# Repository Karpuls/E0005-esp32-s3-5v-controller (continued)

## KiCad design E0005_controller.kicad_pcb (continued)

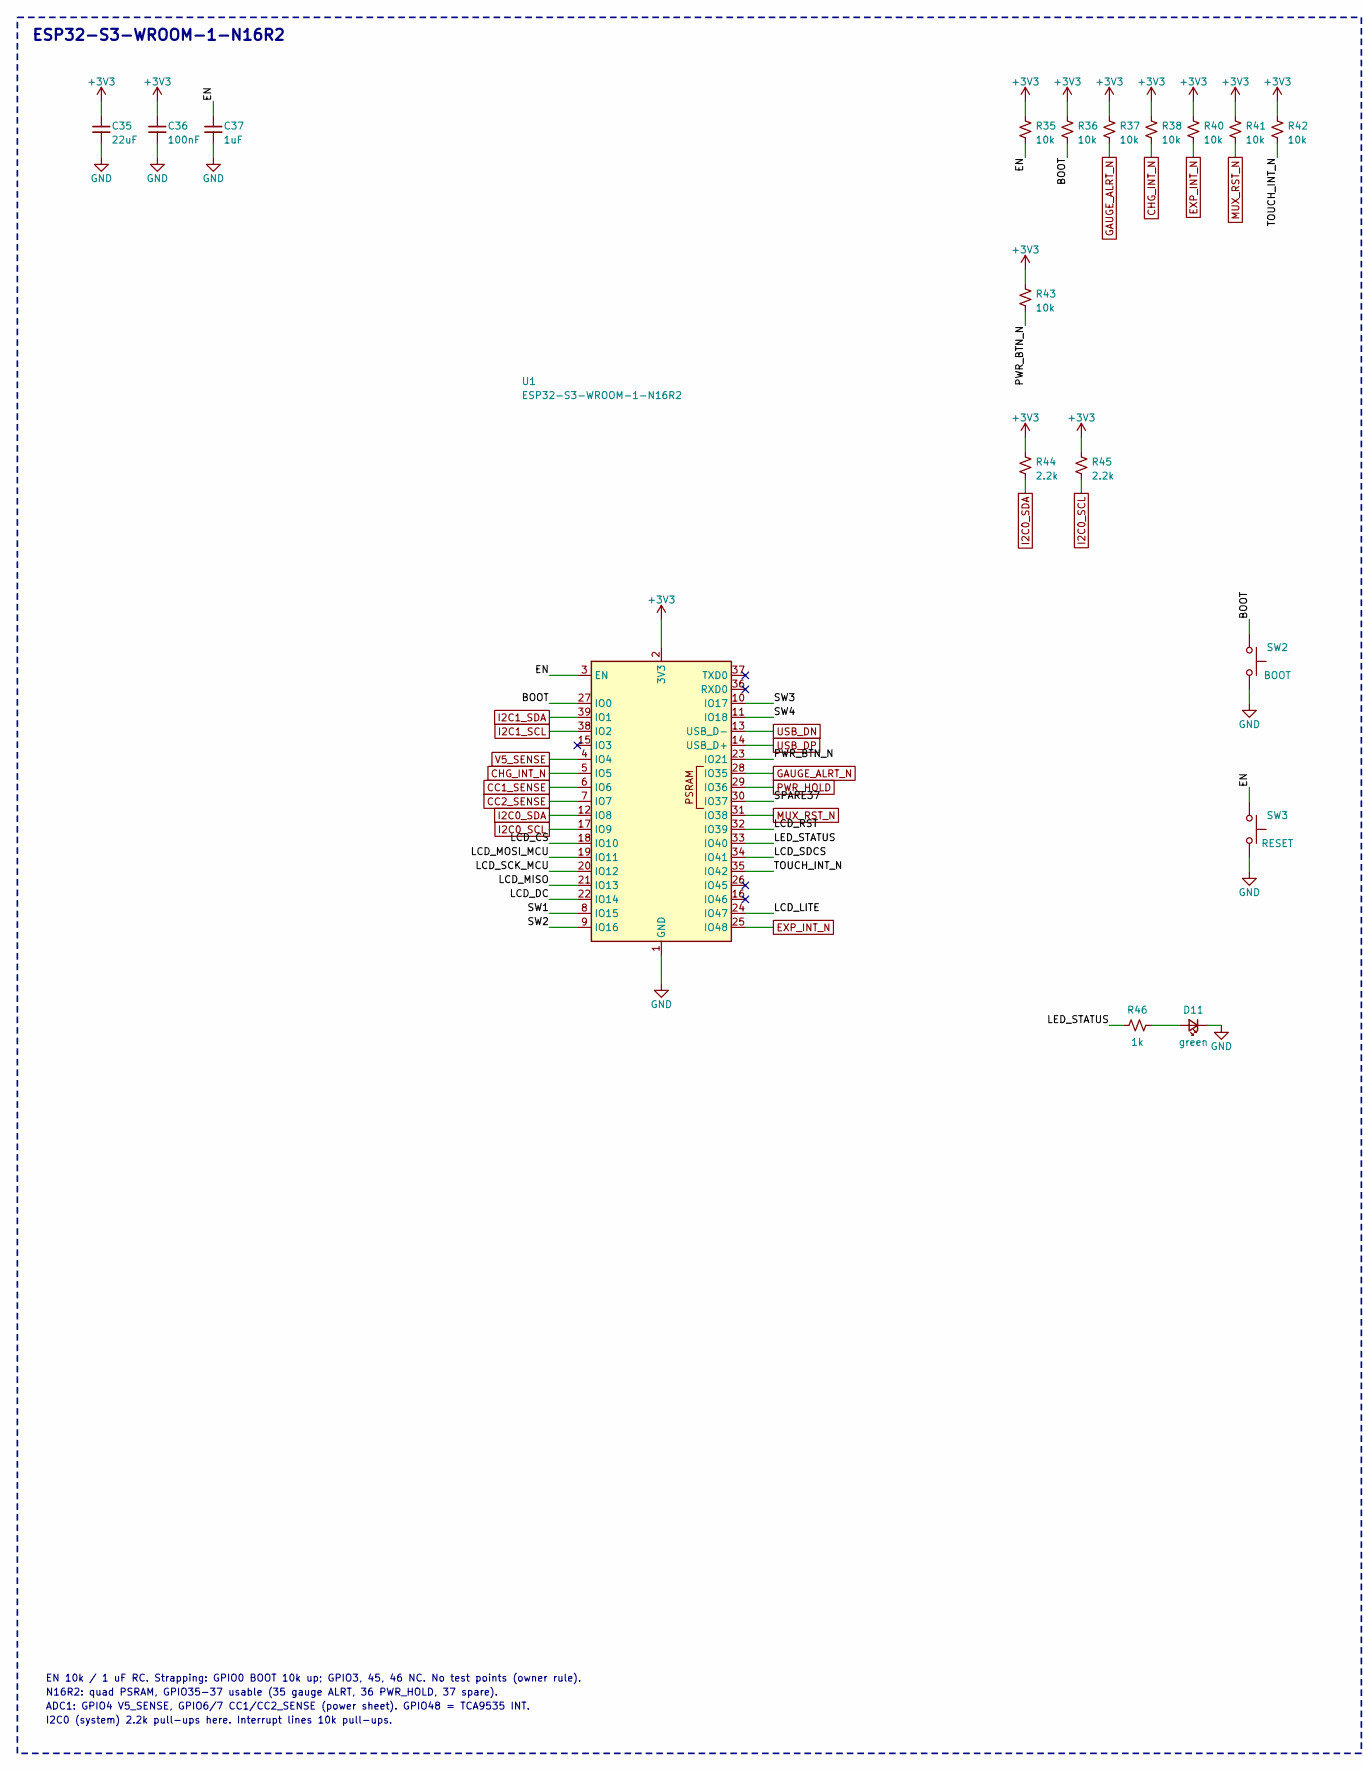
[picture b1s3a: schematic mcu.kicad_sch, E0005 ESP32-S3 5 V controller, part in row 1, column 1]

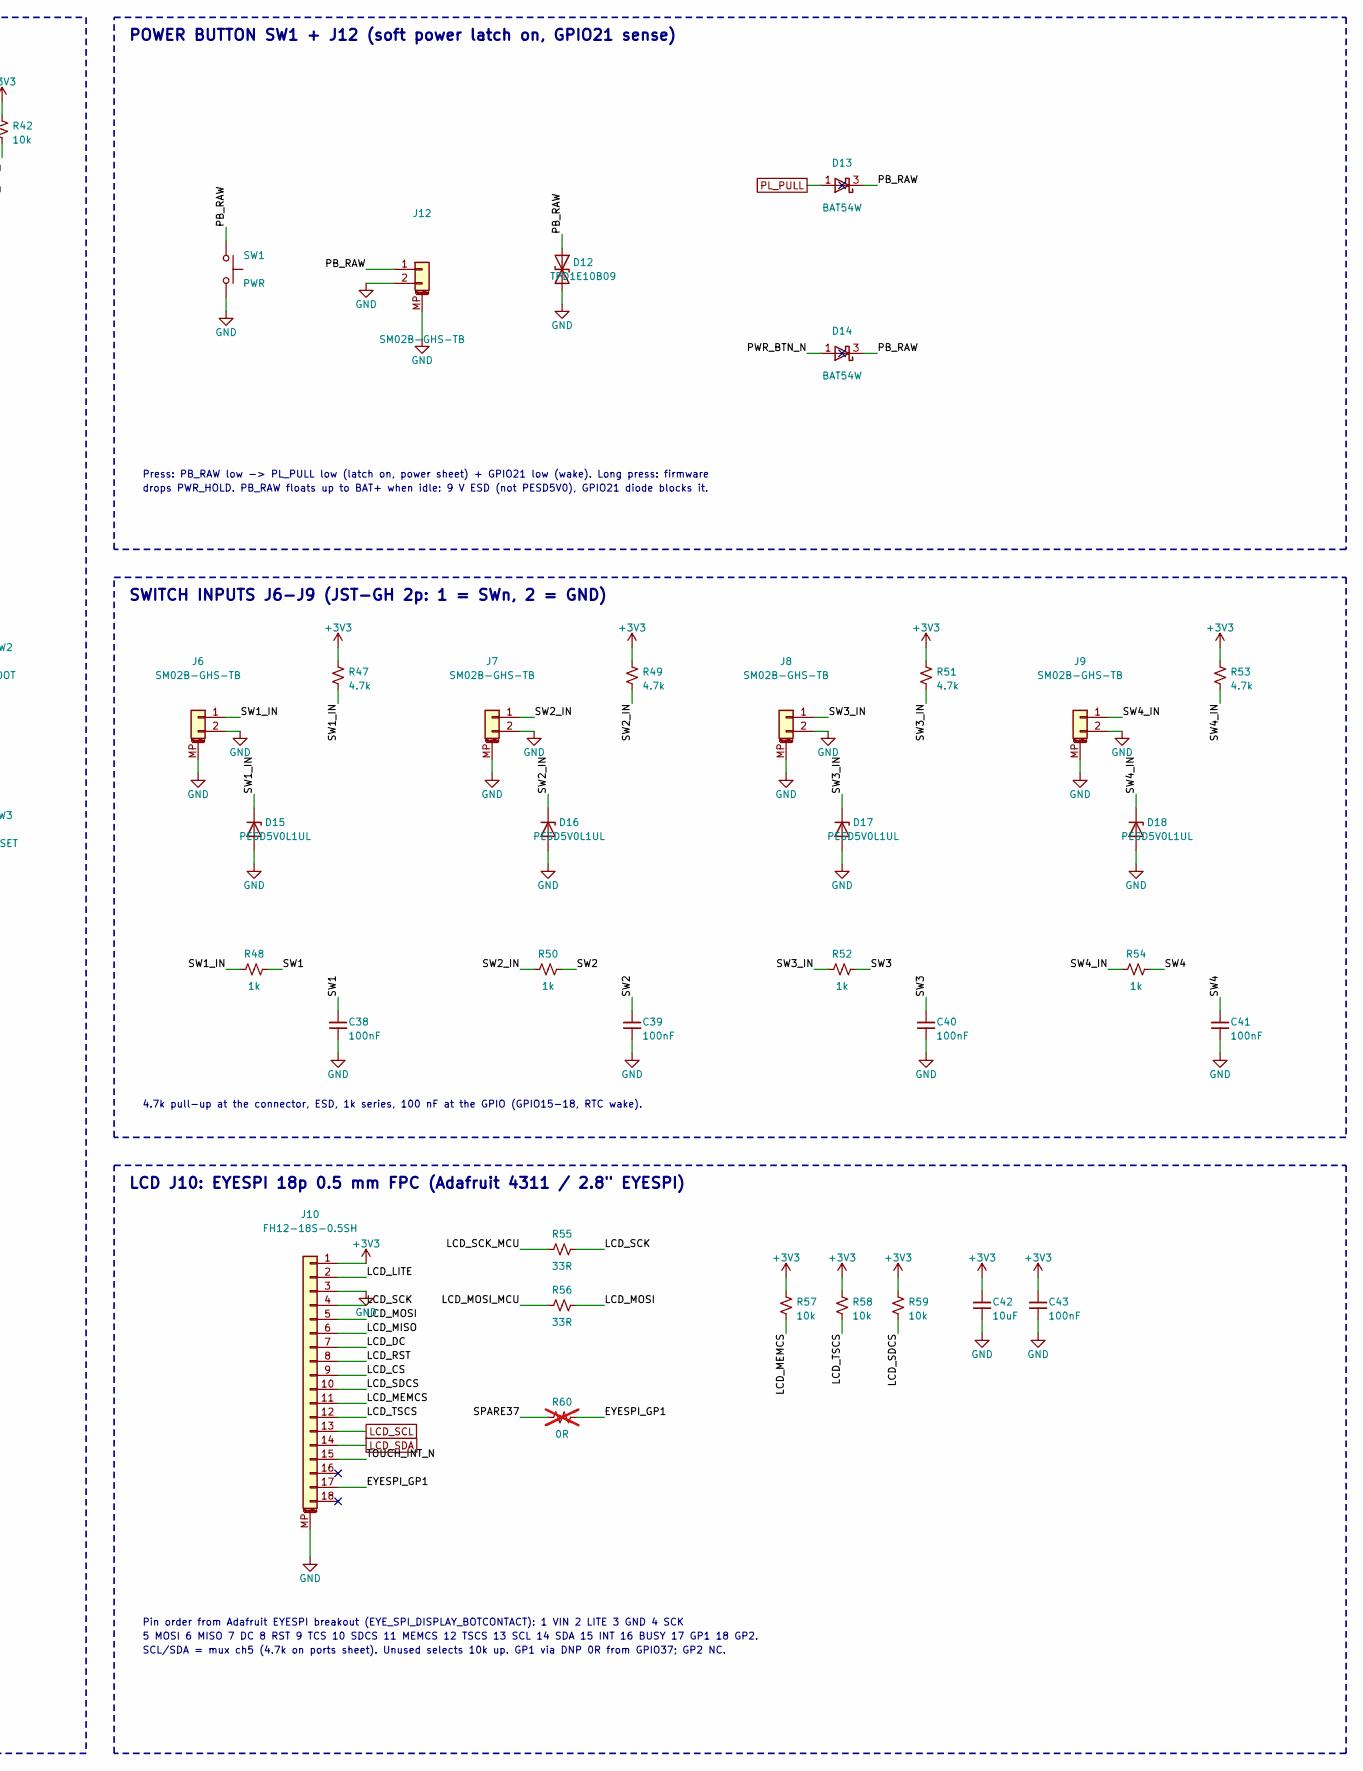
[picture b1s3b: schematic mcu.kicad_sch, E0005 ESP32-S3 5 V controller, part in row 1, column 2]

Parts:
C35: 22uF; C_0805_2012Metric; Voltage 6.3V; MPN CL21A226KQCLRNC
C36, C38, C39, C40, C41, C43: 100nF; C_0402_1005Metric; Voltage 50V; MPN GRM155R71H104KE14D
C37: 1uF; C_0402_1005Metric; MPN CL05A105KP5NNNC
C42: 10uF; C_0805_2012Metric; Voltage 25V; MPN TMK212BBJ106MG-T
D11: green; LED_0603_1608Metric; MPN LTST-C191KGKT
D12: TPD1E10B09; D_0402_1005Metric; MPN TPD1E10B09DPYR
D13, D14: BAT54W; SOT-323_SC-70; MPN BAT54W,135
D15, D16, D17, D18: PESD5V0L1UL; D_SOD-882; MPN PESD5V0L1UL,315
J6, J7, J8, J9, J12: SM02B-GHS-TB; JST_GH_SM02B-GHS-TB_1x02-1MP_P1.25mm_Horizontal; MPN SM02B-GHS-TB
J10: FH12-18S-0.5SH; Hirose_FH12-18S-0.5SH_1x18-1MP_P0.50mm_Horizontal; MPN FH12-18S-0.5SH(55)
R35, R36, R37, R38, R40, R41, R42, R43, R57, R58, R59: 10k; R_0402_1005Metric; MPN RC0402FR-0710KL
R44, R45: 2.2k; R_0402_1005Metric; MPN RC0402FR-072K2L
R46, R48, R50, R52, R54: 1k; R_0402_1005Metric; MPN RC0402FR-071KL
R47, R49, R51, R53: 4.7k; R_0402_1005Metric; MPN RK73H1ETTP4701F
R55, R56: 33R; R_0402_1005Metric; MPN RC0402FR-0733RL
R60: 0R; R_0402_1005Metric; MPN RC0402JR-070RL; not fitted
SW1: PWR; SW_SPST_PTS810; MPN PTS810SJM250SMTR LFS
SW2: BOOT; SW_SPST_PTS810; MPN PTS810SJM250SMTR LFS
SW3: RESET; SW_SPST_PTS810; MPN PTS810SJM250SMTR LFS
U1: ESP32-S3-WROOM-1-N16R2; ESP32-S3-WROOM-1; MPN ESP32-S3-WROOM-1-N16R2

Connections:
+3V3: C35.1, C36.1, C42.1, C43.1, J10.1, R35.1, R36.1, R37.1, R38.1, R40.1, R41.1, R42.1, R43.1, R44.1, R45.1, R47.1, R49.1, R51.1, R53.1, R57.1, R58.1, R59.1, U1.2 (3V3); also elsewhere on the board
/MCU, UI, LCD, switches/BOOT: R36.2, SW2.1, U1.27 (IO0)
/MCU, UI, LCD, switches/EN: C37.1, R35.2, SW3.1, U1.3 (EN)
/MCU, UI, LCD, switches/EYESPI_GP1: J10.17, R60.2
/MCU, UI, LCD, switches/LCD_CS: J10.9, U1.18 (IO10)
/MCU, UI, LCD, switches/LCD_DC: J10.7, U1.22 (IO14)
/MCU, UI, LCD, switches/LCD_LITE: J10.2, U1.24 (IO47)
/MCU, UI, LCD, switches/LCD_MEMCS: J10.11, R57.2
/MCU, UI, LCD, switches/LCD_MISO: J10.6, U1.21 (IO13)
/MCU, UI, LCD, switches/LCD_MOSI: J10.5, R56.2
/MCU, UI, LCD, switches/LCD_MOSI_MCU: R56.1, U1.19 (IO11)
/MCU, UI, LCD, switches/LCD_RST: J10.8, U1.32 (IO39)
/MCU, UI, LCD, switches/LCD_SCK: J10.4, R55.2
/MCU, UI, LCD, switches/LCD_SCK_MCU: R55.1, U1.20 (IO12)
/MCU, UI, LCD, switches/LCD_SDCS: J10.10, R59.2, U1.34 (IO41)
/MCU, UI, LCD, switches/LCD_TSCS: J10.12, R58.2
/MCU, UI, LCD, switches/LED_STATUS: R46.1, U1.33 (IO40)
/MCU, UI, LCD, switches/PB_RAW: D12.1 (A1), D13.3 (K), D14.3 (K), J12.1, SW1.1
/MCU, UI, LCD, switches/PWR_BTN_N: D14.1 (A), R43.2, U1.23 (IO21)
/MCU, UI, LCD, switches/SPARE37: R60.1, U1.30 (IO37)
/MCU, UI, LCD, switches/SW1: C38.1, R48.2, U1.8 (IO15)
/MCU, UI, LCD, switches/SW1_IN: D15.1 (K), J6.1, R47.2, R48.1
/MCU, UI, LCD, switches/SW2: C39.1, R50.2, U1.9 (IO16)
/MCU, UI, LCD, switches/SW2_IN: D16.1 (K), J7.1, R49.2, R50.1
/MCU, UI, LCD, switches/SW3: C40.1, R52.2, U1.10 (IO17)
/MCU, UI, LCD, switches/SW3_IN: D17.1 (K), J8.1, R51.2, R52.1
/MCU, UI, LCD, switches/SW4: C41.1, R54.2, U1.11 (IO18)
/MCU, UI, LCD, switches/SW4_IN: D18.1 (K), J9.1, R53.2, R54.1
/MCU, UI, LCD, switches/TOUCH_INT_N: J10.15, R42.2, U1.35 (IO42)
CC1_SENSE: U1.6 (IO6); also elsewhere on the board
CC2_SENSE: U1.7 (IO7); also elsewhere on the board
CHG_INT_N: R38.2, U1.5 (IO5); also elsewhere on the board
EXP_INT_N: R40.2, U1.25 (IO48); also elsewhere on the board
GAUGE_ALRT_N: R37.2, U1.28 (IO35); also elsewhere on the board
GND: C35.2, C36.2, C37.2, C38.2, C39.2, C40.2, C41.2, C42.2, C43.2, D11.1 (K), D12.2 (A2), D15.2 (A), D16.2 (A), D17.2 (A), D18.2 (A), J6.2, J6.MP (MountPin), J7.2, J7.MP (MountPin), J8.2, J8.MP (MountPin), J9.2, J9.MP (MountPin), J10.3, J10.MP (MountPin), J12.2, J12.MP (MountPin), SW1.2, SW2.2, SW3.2, U1.1 (GND), U1.40 (GND), U1.41 (GND); also elsewhere on the board
I2C0_SCL: R45.2, U1.17 (IO9); also elsewhere on the board
I2C0_SDA: R44.2, U1.12 (IO8); also elsewhere on the board
I2C1_SCL: U1.38 (IO2); also elsewhere on the board
I2C1_SDA: U1.39 (IO1); also elsewhere on the board
LCD_SCL: J10.13; also elsewhere on the board
LCD_SDA: J10.14; also elsewhere on the board
MUX_RST_N: R41.2, U1.31 (IO38); also elsewhere on the board
unnamed: D11.2 (A), R46.2
PL_PULL: D13.1 (A); also elsewhere on the board
PWR_HOLD: U1.29 (IO36); also elsewhere on the board
USB_DN: U1.13 (USB_D-); also elsewhere on the board
USB_DP: U1.14 (USB_D+); also elsewhere on the board
V5_SENSE: U1.4 (IO4); also elsewhere on the board

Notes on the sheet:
ESP32-S3-WROOM-1-N16R2
EN 10k / 1 uF RC. Strapping: GPIO0 BOOT 10k up; GPIO3, 45, 46 NC. No test points (owner rule).
N16R2: quad PSRAM, GPIO35-37 usable (35 gauge ALRT, 36 PWR_HOLD, 37 spare).
ADC1: GPIO4 V5_SENSE, GPIO6/7 CC1/CC2_SENSE (power sheet). GPIO48 = TCA9535 INT.
I2C0 (system) 2.2k pull-ups here. Interrupt lines 10k pull-ups.
POWER BUTTON SW1 + J12 (soft power latch on, GPIO21 sense)
Press: PB_RAW low -> PL_PULL low (latch on, power sheet) + GPIO21 low (wake). Long press: firmware
drops PWR_HOLD. PB_RAW floats up to BAT+ when idle: 9 V ESD (not PESD5V0), GPIO21 diode blocks it.
SWITCH INPUTS J6-J9 (JST-GH 2p: 1 = SWn, 2 = GND)
4.7k pull-up at the connector, ESD, 1k series, 100 nF at the GPIO (GPIO15-18, RTC wake).
LCD J10: EYESPI 18p 0.5 mm FPC (Adafruit 4311 / 2.8" EYESPI)
Pin order from Adafruit EYESPI breakout (EYE_SPI_DISPLAY_BOTCONTACT): 1 VIN 2 LITE 3 GND 4 SCK
5 MOSI 6 MISO 7 DC 8 RST 9 TCS 10 SDCS 11 MEMCS 12 TSCS 13 SCL 14 SDA 15 INT 16 BUSY 17 GP1 18 GP2.
SCL/SDA = mux ch5 (4.7k on ports sheet). Unused selects 10k up. GP1 via DNP 0R from GPIO37; GP2 NC.

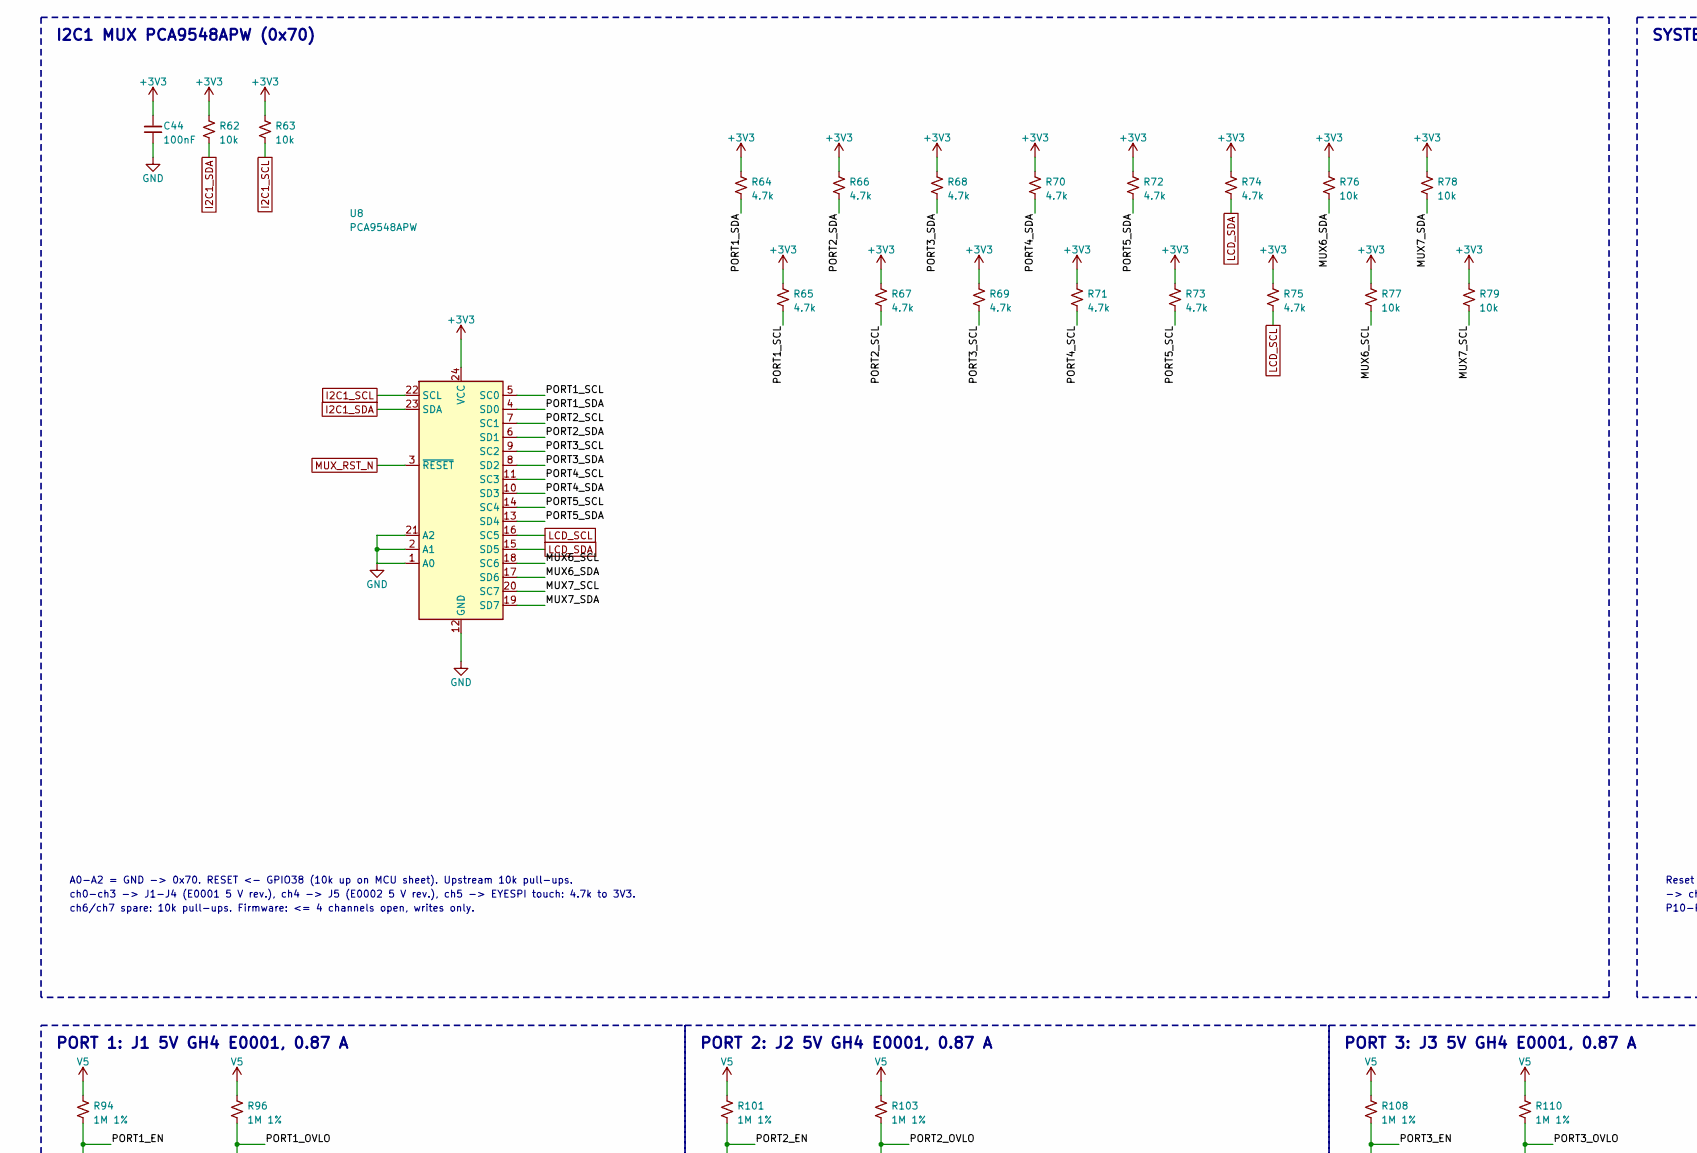
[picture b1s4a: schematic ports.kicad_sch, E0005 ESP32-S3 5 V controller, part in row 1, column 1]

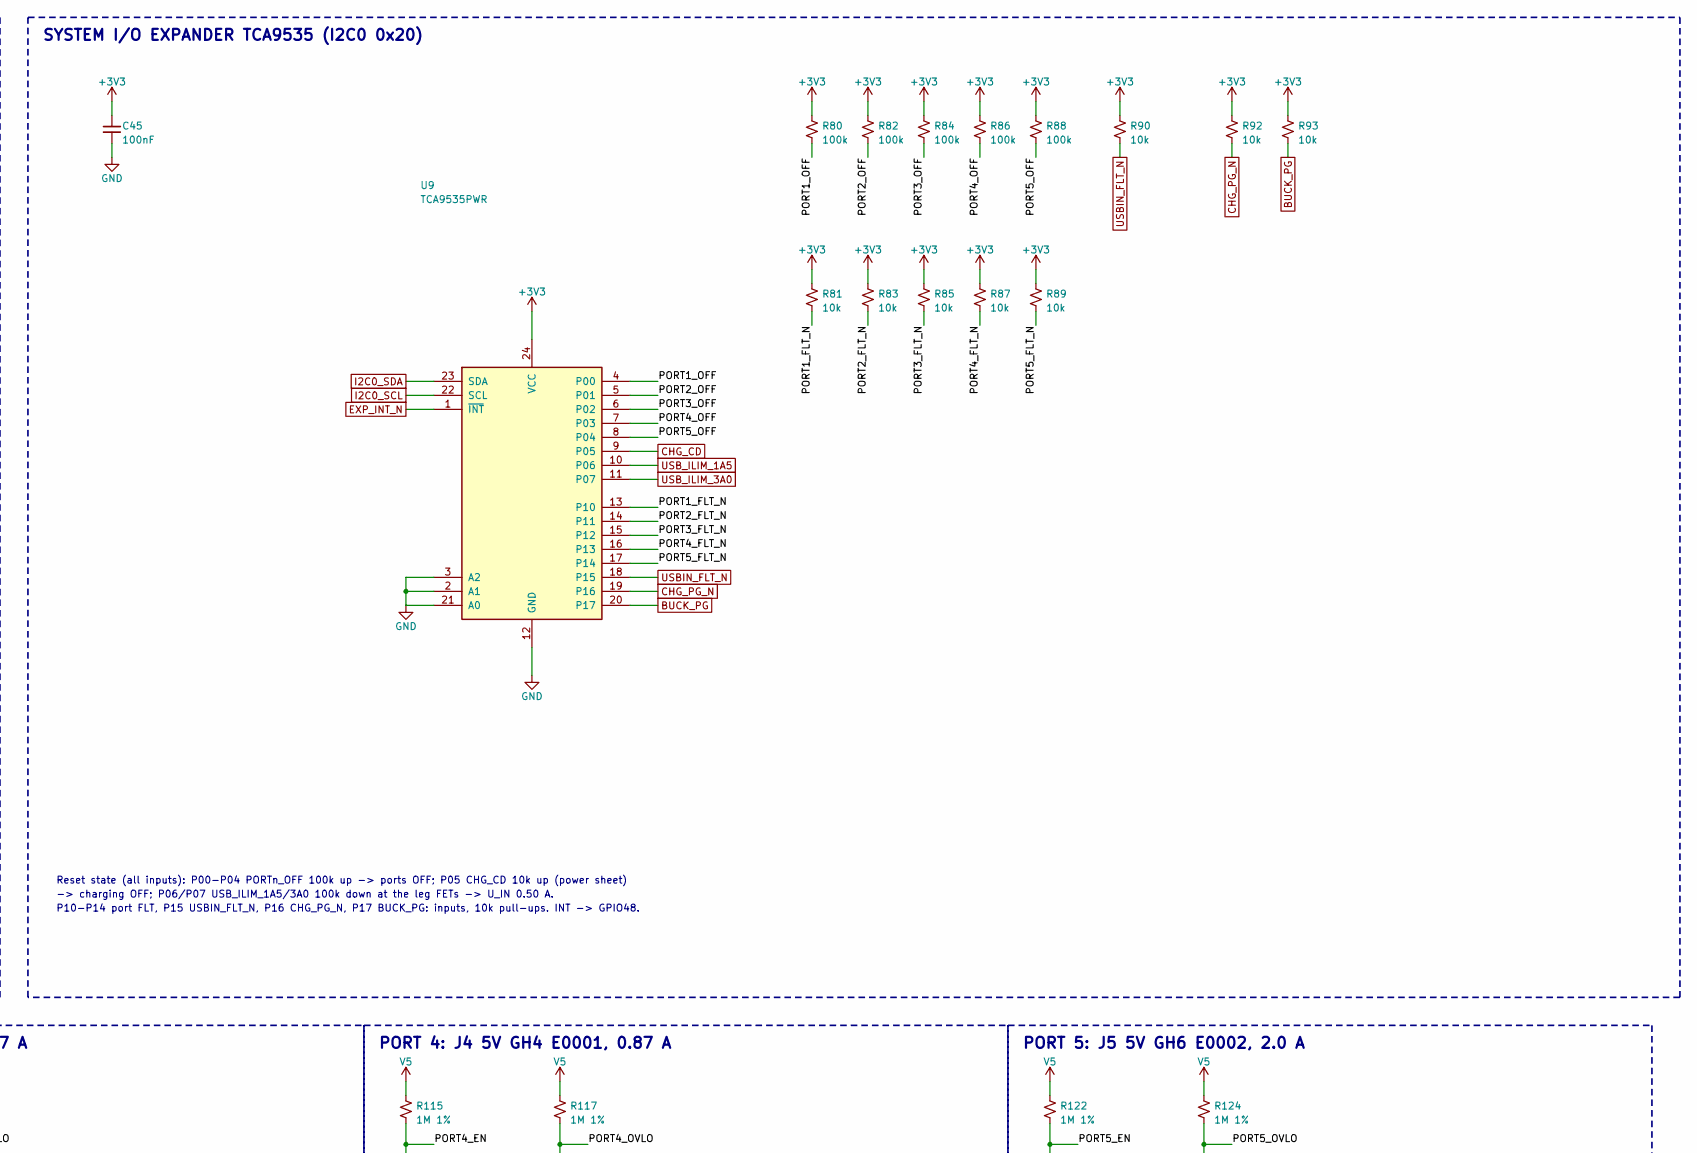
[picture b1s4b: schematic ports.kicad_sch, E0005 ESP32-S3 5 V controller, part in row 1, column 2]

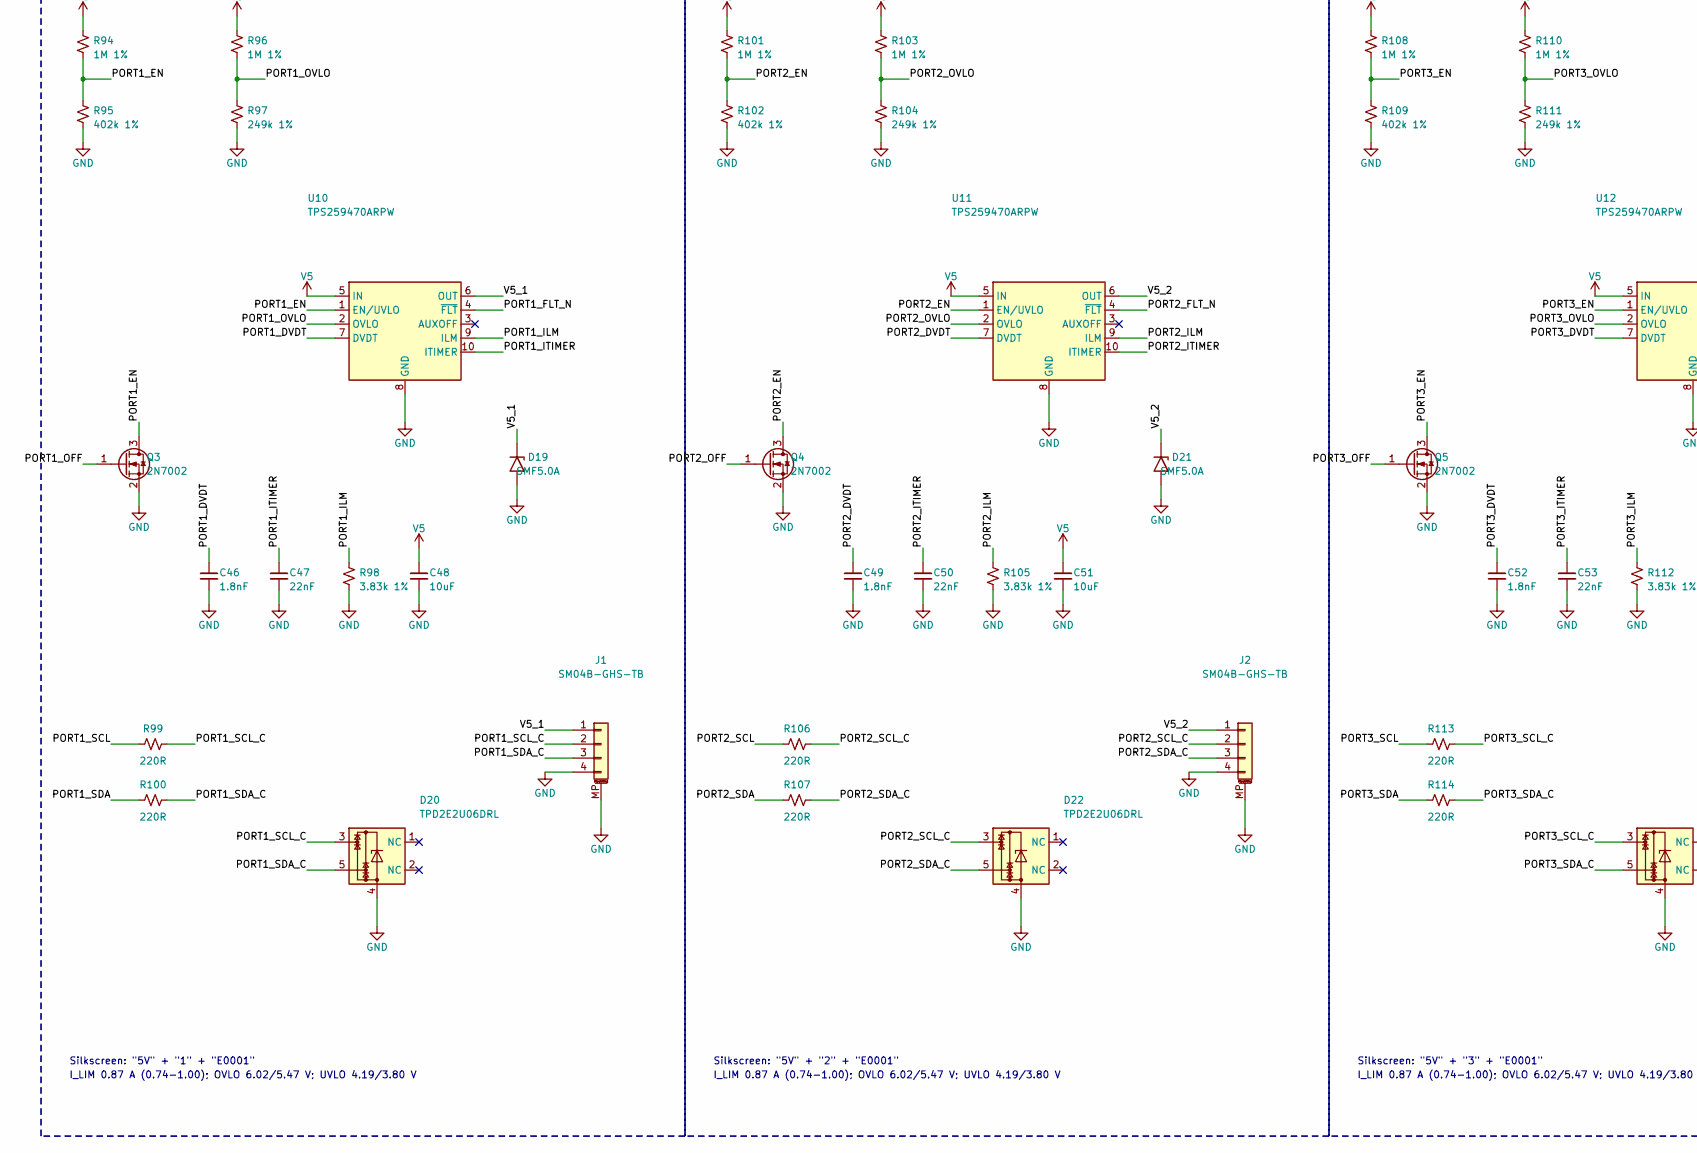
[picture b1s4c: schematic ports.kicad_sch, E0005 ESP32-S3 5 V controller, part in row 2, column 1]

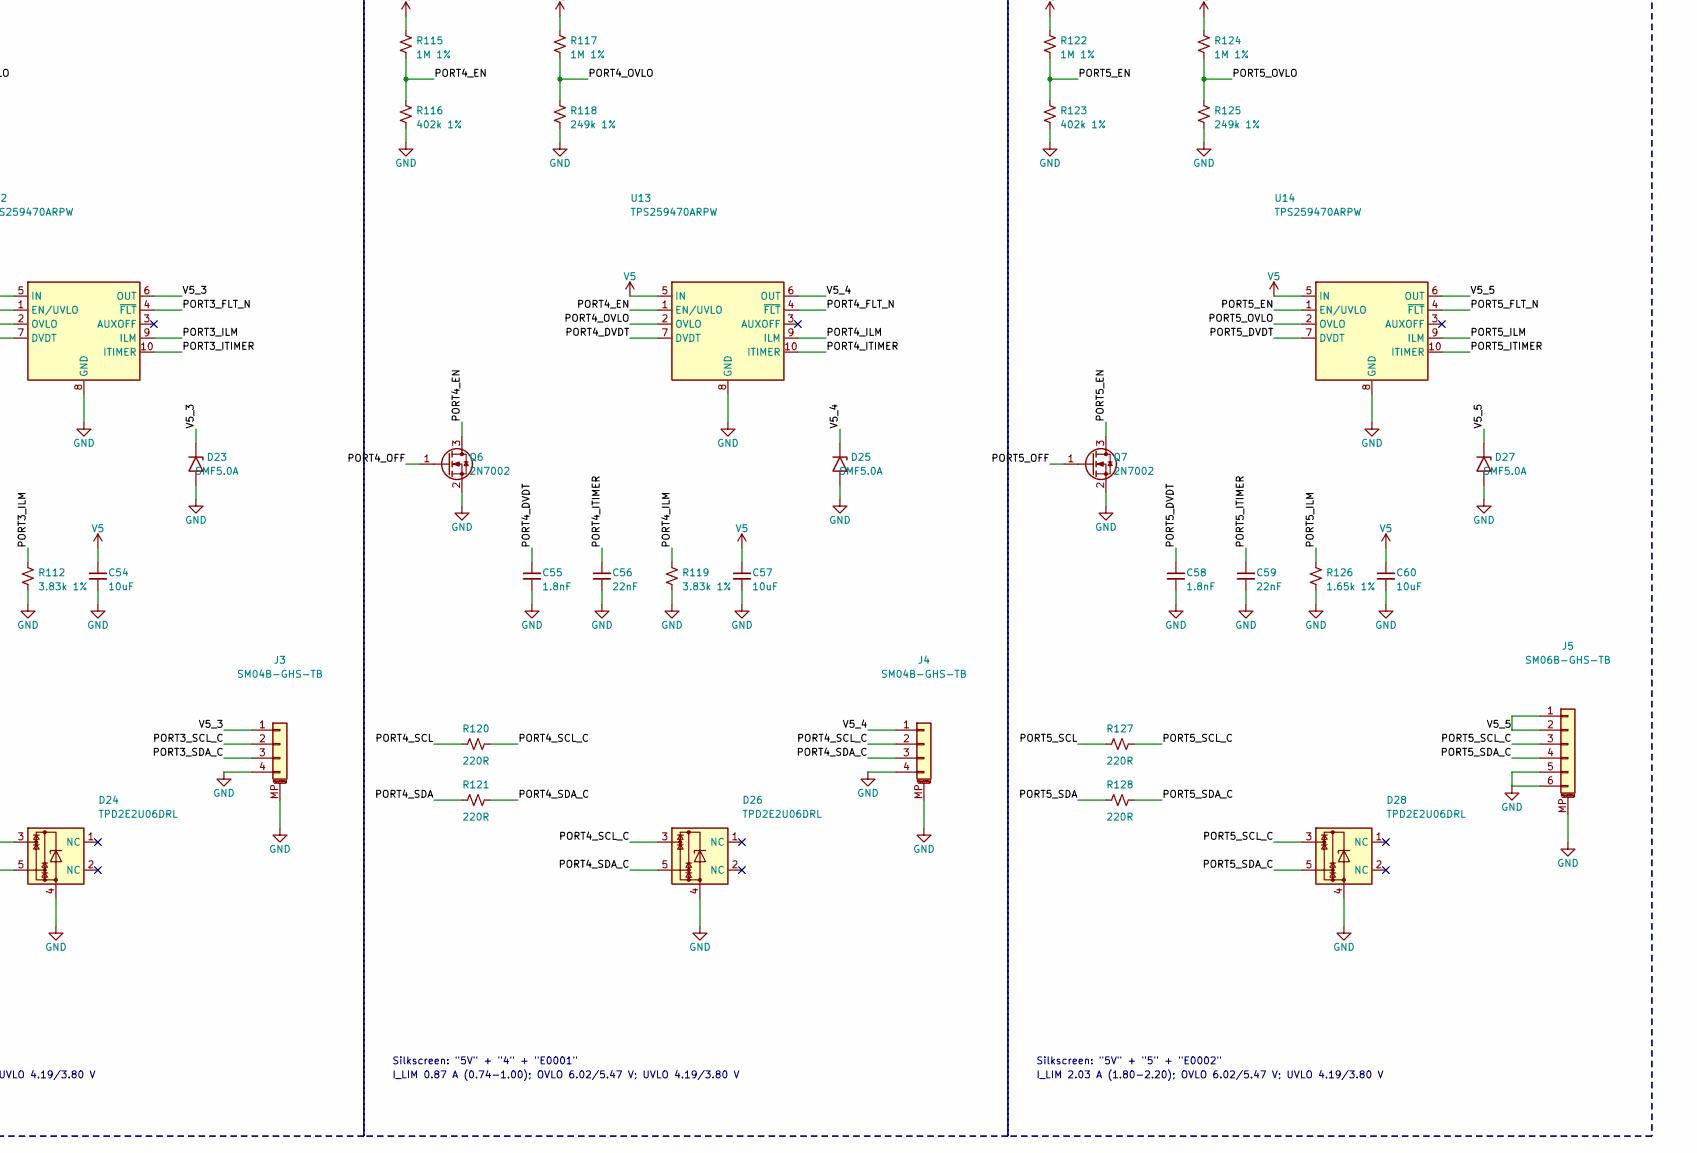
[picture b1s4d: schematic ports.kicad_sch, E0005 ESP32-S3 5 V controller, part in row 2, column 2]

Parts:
C44, C45: 100nF; C_0402_1005Metric; Voltage 50V; MPN GRM155R71H104KE14D
C46, C49, C52, C55, C58: 1.8nF; C_0402_1005Metric; Voltage 50V; MPN C0402C182K5RACTU
C47, C50, C53, C56, C59: 22nF; C_0402_1005Metric; Voltage 50V; MPN GRM155R71H223KA12D
C48, C51, C54, C57, C60: 10uF; C_0805_2012Metric; Voltage 25V; MPN TMK212BBJ106MG-T
D19, D21, D23, D25, D27: SMF5.0A; D_SOD-123F; MPN SMF5.0A
D20, D22, D24, D26, D28: TPD2E2U06DRL; SOT-553; MPN TPD2E2U06DRLR
J1, J2, J3, J4: SM04B-GHS-TB; JST_GH_SM04B-GHS-TB_1x04-1MP_P1.25mm_Horizontal; MPN SM04B-GHS-TB
J5: SM06B-GHS-TB; JST_GH_SM06B-GHS-TB_1x06-1MP_P1.25mm_Horizontal; MPN SM06B-GHS-TB(LF)(SN)
Q3, Q4, Q5, Q6, Q7: 2N7002; SOT-23; MPN 2N7002-7-F
R62, R63, R76, R77, R78, R79, R81, R83, R85, R87, R89, R90, R92, R93: 10k; R_0402_1005Metric; MPN RC0402FR-0710KL
R64, R65, R66, R67, R68, R69, R70, R71, R72, R73, R74, R75: 4.7k; R_0402_1005Metric; MPN RK73H1ETTP4701F
R80, R82, R84, R86, R88: 100k; R_0402_1005Metric; MPN RC0402FR-07100KL
R94, R96, R101, R103, R108, R110, R115, R117, R122, R124: 1M 1%; R_0402_1005Metric; MPN RC0402FR-071ML
R95, R102, R109, R116, R123: 402k 1%; R_0402_1005Metric; MPN RC0402FR-07402KL
R97, R104, R111, R118, R125: 249k 1%; R_0402_1005Metric; MPN RC0402FR-07249KL
R98, R105, R112, R119: 3.83k 1%; R_0402_1005Metric; MPN RC0402FR-073K83L
R99, R100, R106, R107, R113, R114, R120, R121, R127, R128: 220R; R_0402_1005Metric; MPN RC0402FR-07220RL
R126: 1.65k 1%; R_0402_1005Metric; MPN RC0402FR-071K65L
U8: PCA9548APW; TSSOP-24_4.4x7.8mm_P0.65mm; MPN PCA9548APW,118
U9: TCA9535PWR; TSSOP-24_4.4x7.8mm_P0.65mm; MPN TCA9535PWR
U10, U11, U12, U13, U14: TPS259470ARPW; TI_RPW0010A_VQFN-HR-10_2x2mm_P0.475mm; MPN TPS259470ARPWR

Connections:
+3V3: C44.1, C45.1, R62.1, R63.1, R64.1, R65.1, R66.1, R67.1, R68.1, R69.1, R70.1, R71.1, R72.1, R73.1, R74.1, R75.1, R76.1, R77.1, R78.1, R79.1, R80.1, R81.1, R82.1, R83.1, R84.1, R85.1, R86.1, R87.1, R88.1, R89.1, R90.1, R92.1, R93.1, U8.24 (VCC), U9.24 (VCC); also elsewhere on the board
/I2C mux, expander, 5 V peripheral ports/MUX6_SCL: R77.2, U8.18 (SC6)
/I2C mux, expander, 5 V peripheral ports/MUX6_SDA: R76.2, U8.17 (SD6)
/I2C mux, expander, 5 V peripheral ports/MUX7_SCL: R79.2, U8.20 (SC7)
/I2C mux, expander, 5 V peripheral ports/MUX7_SDA: R78.2, U8.19 (SD7)
/I2C mux, expander, 5 V peripheral ports/PORT1_DVDT: C46.1, U10.7 (DVDT)
/I2C mux, expander, 5 V peripheral ports/PORT1_EN: Q3.3 (D), R94.2, R95.1, U10.1 (EN/UVLO)
/I2C mux, expander, 5 V peripheral ports/PORT1_FLT_N: R81.2, U9.13 (P10), U10.4 (~FLT)
/I2C mux, expander, 5 V peripheral ports/PORT1_ILM: R98.1, U10.9 (ILM)
/I2C mux, expander, 5 V peripheral ports/PORT1_ITIMER: C47.1, U10.10 (ITIMER)
/I2C mux, expander, 5 V peripheral ports/PORT1_OFF: Q3.1 (G), R80.2, U9.4 (P00)
/I2C mux, expander, 5 V peripheral ports/PORT1_OVLO: R96.2, R97.1, U10.2 (OVLO)
/I2C mux, expander, 5 V peripheral ports/PORT1_SCL: R65.2, R99.1, U8.5 (SC0)
/I2C mux, expander, 5 V peripheral ports/PORT1_SCL_C: D20.3, J1.2, R99.2
/I2C mux, expander, 5 V peripheral ports/PORT1_SDA: R64.2, R100.1, U8.4 (SD0)
/I2C mux, expander, 5 V peripheral ports/PORT1_SDA_C: D20.5, J1.3, R100.2
/I2C mux, expander, 5 V peripheral ports/PORT2_DVDT: C49.1, U11.7 (DVDT)
/I2C mux, expander, 5 V peripheral ports/PORT2_EN: Q4.3 (D), R101.2, R102.1, U11.1 (EN/UVLO)
/I2C mux, expander, 5 V peripheral ports/PORT2_FLT_N: R83.2, U9.14 (P11), U11.4 (~FLT)
/I2C mux, expander, 5 V peripheral ports/PORT2_ILM: R105.1, U11.9 (ILM)
/I2C mux, expander, 5 V peripheral ports/PORT2_ITIMER: C50.1, U11.10 (ITIMER)
/I2C mux, expander, 5 V peripheral ports/PORT2_OFF: Q4.1 (G), R82.2, U9.5 (P01)
/I2C mux, expander, 5 V peripheral ports/PORT2_OVLO: R103.2, R104.1, U11.2 (OVLO)
/I2C mux, expander, 5 V peripheral ports/PORT2_SCL: R67.2, R106.1, U8.7 (SC1)
/I2C mux, expander, 5 V peripheral ports/PORT2_SCL_C: D22.3, J2.2, R106.2
/I2C mux, expander, 5 V peripheral ports/PORT2_SDA: R66.2, R107.1, U8.6 (SD1)
/I2C mux, expander, 5 V peripheral ports/PORT2_SDA_C: D22.5, J2.3, R107.2
/I2C mux, expander, 5 V peripheral ports/PORT3_DVDT: C52.1, U12.7 (DVDT)
/I2C mux, expander, 5 V peripheral ports/PORT3_EN: Q5.3 (D), R108.2, R109.1, U12.1 (EN/UVLO)
/I2C mux, expander, 5 V peripheral ports/PORT3_FLT_N: R85.2, U9.15 (P12), U12.4 (~FLT)
/I2C mux, expander, 5 V peripheral ports/PORT3_ILM: R112.1, U12.9 (ILM)
/I2C mux, expander, 5 V peripheral ports/PORT3_ITIMER: C53.1, U12.10 (ITIMER)
/I2C mux, expander, 5 V peripheral ports/PORT3_OFF: Q5.1 (G), R84.2, U9.6 (P02)
/I2C mux, expander, 5 V peripheral ports/PORT3_OVLO: R110.2, R111.1, U12.2 (OVLO)
/I2C mux, expander, 5 V peripheral ports/PORT3_SCL: R69.2, R113.1, U8.9 (SC2)
/I2C mux, expander, 5 V peripheral ports/PORT3_SCL_C: D24.3, J3.2, R113.2
/I2C mux, expander, 5 V peripheral ports/PORT3_SDA: R68.2, R114.1, U8.8 (SD2)
/I2C mux, expander, 5 V peripheral ports/PORT3_SDA_C: D24.5, J3.3, R114.2
/I2C mux, expander, 5 V peripheral ports/PORT4_DVDT: C55.1, U13.7 (DVDT)
/I2C mux, expander, 5 V peripheral ports/PORT4_EN: Q6.3 (D), R115.2, R116.1, U13.1 (EN/UVLO)
/I2C mux, expander, 5 V peripheral ports/PORT4_FLT_N: R87.2, U9.16 (P13), U13.4 (~FLT)
/I2C mux, expander, 5 V peripheral ports/PORT4_ILM: R119.1, U13.9 (ILM)
/I2C mux, expander, 5 V peripheral ports/PORT4_ITIMER: C56.1, U13.10 (ITIMER)
/I2C mux, expander, 5 V peripheral ports/PORT4_OFF: Q6.1 (G), R86.2, U9.7 (P03)
/I2C mux, expander, 5 V peripheral ports/PORT4_OVLO: R117.2, R118.1, U13.2 (OVLO)
/I2C mux, expander, 5 V peripheral ports/PORT4_SCL: R71.2, R120.1, U8.11 (SC3)
/I2C mux, expander, 5 V peripheral ports/PORT4_SCL_C: D26.3, J4.2, R120.2
/I2C mux, expander, 5 V peripheral ports/PORT4_SDA: R70.2, R121.1, U8.10 (SD3)
/I2C mux, expander, 5 V peripheral ports/PORT4_SDA_C: D26.5, J4.3, R121.2
/I2C mux, expander, 5 V peripheral ports/PORT5_DVDT: C58.1, U14.7 (DVDT)
/I2C mux, expander, 5 V peripheral ports/PORT5_EN: Q7.3 (D), R122.2, R123.1, U14.1 (EN/UVLO)
/I2C mux, expander, 5 V peripheral ports/PORT5_FLT_N: R89.2, U9.17 (P14), U14.4 (~FLT)
/I2C mux, expander, 5 V peripheral ports/PORT5_ILM: R126.1, U14.9 (ILM)
/I2C mux, expander, 5 V peripheral ports/PORT5_ITIMER: C59.1, U14.10 (ITIMER)
/I2C mux, expander, 5 V peripheral ports/PORT5_OFF: Q7.1 (G), R88.2, U9.8 (P04)
/I2C mux, expander, 5 V peripheral ports/PORT5_OVLO: R124.2, R125.1, U14.2 (OVLO)
/I2C mux, expander, 5 V peripheral ports/PORT5_SCL: R73.2, R127.1, U8.14 (SC4)
/I2C mux, expander, 5 V peripheral ports/PORT5_SCL_C: D28.3, J5.3, R127.2
/I2C mux, expander, 5 V peripheral ports/PORT5_SDA: R72.2, R128.1, U8.13 (SD4)
/I2C mux, expander, 5 V peripheral ports/PORT5_SDA_C: D28.5, J5.4, R128.2
/I2C mux, expander, 5 V peripheral ports/V5_1: D19.1 (A1), J1.1, U10.6 (OUT)
/I2C mux, expander, 5 V peripheral ports/V5_2: D21.1 (A1), J2.1, U11.6 (OUT)
/I2C mux, expander, 5 V peripheral ports/V5_3: D23.1 (A1), J3.1, U12.6 (OUT)
/I2C mux, expander, 5 V peripheral ports/V5_4: D25.1 (A1), J4.1, U13.6 (OUT)
/I2C mux, expander, 5 V peripheral ports/V5_5: D27.1 (A1), J5.1, J5.2, U14.6 (OUT)
BUCK_PG: R93.2, U9.20 (P17); also elsewhere on the board
CHG_CD: U9.9 (P05); also elsewhere on the board
CHG_PG_N: R92.2, U9.19 (P16); also elsewhere on the board
EXP_INT_N: U9.1 (~INT); also elsewhere on the board
GND: C44.2, C45.2, C46.2, C47.2, C48.2, C49.2, C50.2, C51.2, C52.2, C53.2, C54.2, C55.2, C56.2, C57.2, C58.2, C59.2, C60.2, D19.2 (A2), D20.4, D21.2 (A2), D22.4, D23.2 (A2), D24.4, D25.2 (A2), D26.4, D27.2 (A2), D28.4, J1.4, J1.MP (MountPin), J2.4, J2.MP (MountPin), J3.4, J3.MP (MountPin), J4.4, J4.MP (MountPin), J5.5, J5.6, J5.MP (MountPin), Q3.2 (S), Q4.2 (S), Q5.2 (S), Q6.2 (S), Q7.2 (S), R95.2, R97.2, R98.2, R102.2, R104.2, R105.2, R109.2, R111.2, R112.2, R116.2, R118.2, R119.2, R123.2, R125.2, R126.2, U8.1 (A0), U8.2 (A1), U8.12 (GND), U8.21 (A2), U9.2 (A1), U9.3 (A2), U9.12 (GND), U9.21 (A0), U10.8 (GND), U11.8 (GND), U12.8 (GND), U13.8 (GND), U14.8 (GND); also elsewhere on the board
I2C0_SCL: U9.22 (SCL); also elsewhere on the board
I2C0_SDA: U9.23 (SDA); also elsewhere on the board
I2C1_SCL: R63.2, U8.22 (SCL); also elsewhere on the board
I2C1_SDA: R62.2, U8.23 (SDA); also elsewhere on the board
LCD_SCL: R75.2, U8.16 (SC5); also elsewhere on the board
LCD_SDA: R74.2, U8.15 (SD5); also elsewhere on the board
MUX_RST_N: U8.3 (~RESET); also elsewhere on the board
USBIN_FLT_N: R90.2, U9.18 (P15); also elsewhere on the board
USB_ILIM_1A5: U9.10 (P06); also elsewhere on the board
USB_ILIM_3A0: U9.11 (P07); also elsewhere on the board
V5: C48.1, C51.1, C54.1, C57.1, C60.1, R94.1, R96.1, R101.1, R103.1, R108.1, R110.1, R115.1, R117.1, R122.1, R124.1, U10.5 (IN), U11.5 (IN), U12.5 (IN), U13.5 (IN), U14.5 (IN); also elsewhere on the board

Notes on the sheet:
I2C1 MUX PCA9548APW (0x70)
A0-A2 = GND -> 0x70. RESET <- GPIO38 (10k up on MCU sheet). Upstream 10k pull-ups.
ch0-ch3 -> J1-J4 (E0001 5 V rev.), ch4 -> J5 (E0002 5 V rev.), ch5 -> EYESPI touch: 4.7k to 3V3.
ch6/ch7 spare: 10k pull-ups. Firmware: <= 4 channels open, writes only.
SYSTEM I/O EXPANDER TCA9535 (I2C0 0x20)
Reset state (all inputs): P00-P04 PORTn_OFF 100k up -> ports OFF; P05 CHG_CD 10k up (power sheet)
-> charging OFF; P06/P07 USB_ILIM_1A5/3A0 100k down at the leg FETs -> U_IN 0.50 A.
P10-P14 port FLT, P15 USBIN_FLT_N, P16 CHG_PG_N, P17 BUCK_PG: inputs, 10k pull-ups. INT -> GPIO48.
PORT 1: J1 5V GH4 E0001, 0.87 A
Silkscreen: "5V" + "1" + "E0001"
I_LIM 0.87 A (0.74-1.00); OVLO 6.02/5.47 V; UVLO 4.19/3.80 V
PORT 2: J2 5V GH4 E0001, 0.87 A
Silkscreen: "5V" + "2" + "E0001"
PORT 3: J3 5V GH4 E0001, 0.87 A
Silkscreen: "5V" + "3" + "E0001"
PORT 4: J4 5V GH4 E0001, 0.87 A
Silkscreen: "5V" + "4" + "E0001"
PORT 5: J5 5V GH6 E0002, 2.0 A
Silkscreen: "5V" + "5" + "E0002"
I_LIM 2.03 A (1.80-2.20); OVLO 6.02/5.47 V; UVLO 4.19/3.80 V
